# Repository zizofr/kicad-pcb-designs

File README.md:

# KiCad PCB Designs

Two PCB projects designed in KiCad: a digital voltmeter and a 220 V AC LED lamp. Each folder contains the KiCad project, the schematic, the PCB layout and a 3D render.

> **Design process:** both boards are my own designs, created in KiCad with AI-assisted guidance. I use AI as a tutor to learn circuit design, and I work through each block of the circuit to understand it.

## 1. Digital voltmeter (`voltmeter/`)

A voltmeter board built around an **ATmega328P** with a 16 MHz crystal and a 16x2 LCD.

- **Power:** 7805 regulator with reverse-polarity protection
- **Input stage:** resistor divider with a fuse, clamping diodes and a 5.1 V zener to protect the ADC
- **Programming:** ICSP header
- **Layout:** double-sided PCB with routed traces and a ground pour

**Status:** designed in KiCad. [Add whether you assembled and tested it, and the measurement range]

## 2. LED lamp (`led-lamp/`)

A compact LED lamp powered from the 220 V AC mains.

- **Rectification:** MB6S bridge rectifier
- **Lighting:** series string of SMD LEDs
- **Passive parts:** current-limiting and bleeder resistors, smoothing capacitors

**Status:** designed in KiCad. [Add whether you built or tested it]

> ⚠️ **Safety warning:** this circuit connects directly to 220 V mains and has no galvanic isolation. Every part of the circuit can be at mains potential. Do not build or touch it unless you know how to work safely with mains voltage. It is shared for educational purposes only.

## Tools

KiCad (schematic capture, PCB layout, 3D viewer)

## Author

Mohamed Aziz Farhani, IoT Engineering Student at ISITCom Hammam Sousse
[LinkedIn](https://www.linkedin.com/in/mohamed-aziz-farhani-18540a33a)

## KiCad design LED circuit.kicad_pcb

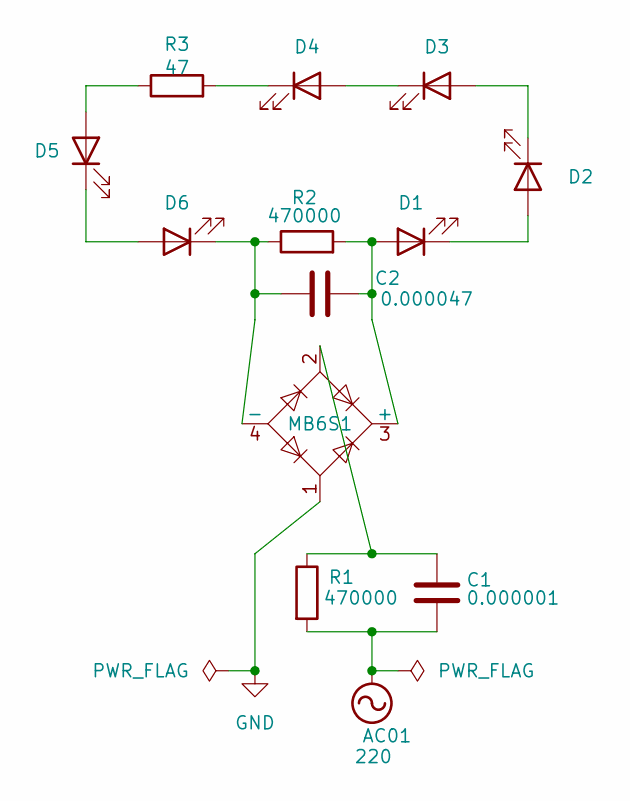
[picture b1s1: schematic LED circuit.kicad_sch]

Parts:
AC01: 220
C1: 0.000001; C_Rect_L18.0mm_W6.0mm_P15.00mm_FKS3_FKP3
C2: 0.000047; C_Radial_D6.3mm_H11.0mm_P2.50mm
D1, D2, D3, D4, D5, D6: LED; LED_PLCC_2835_Handsoldering
MB6S1: TO-269AA
R1, R2: 470000; R_0805_2012Metric_Pad1.20x1.40mm_HandSolder
R3: 47; R_1210_3225Metric_Pad1.30x2.65mm_HandSolder

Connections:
220: AC01.1, C1.2, R1.2
GND: MB6S1.1
unnamed: C1.1, MB6S1.2, R1.1
unnamed: C2.2, D1.2 (A), MB6S1.3 (+), R2.2
unnamed: D1.1 (K), D2.2 (A)
unnamed: D2.1 (K), D3.2 (A)
unnamed: D3.1 (K), D4.2 (A)
unnamed: D4.1 (K), R3.2
unnamed: D5.2 (A), R3.1
unnamed: D5.1 (K), D6.2 (A)
unnamed: C2.1, D6.1 (K), MB6S1.4 (-), R2.1

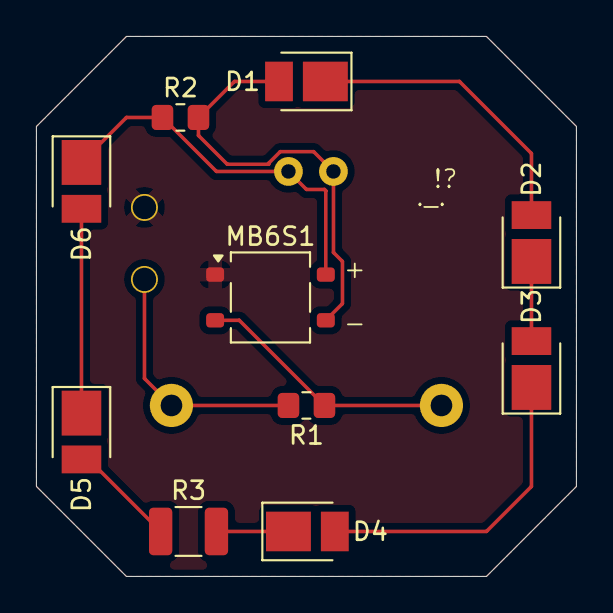
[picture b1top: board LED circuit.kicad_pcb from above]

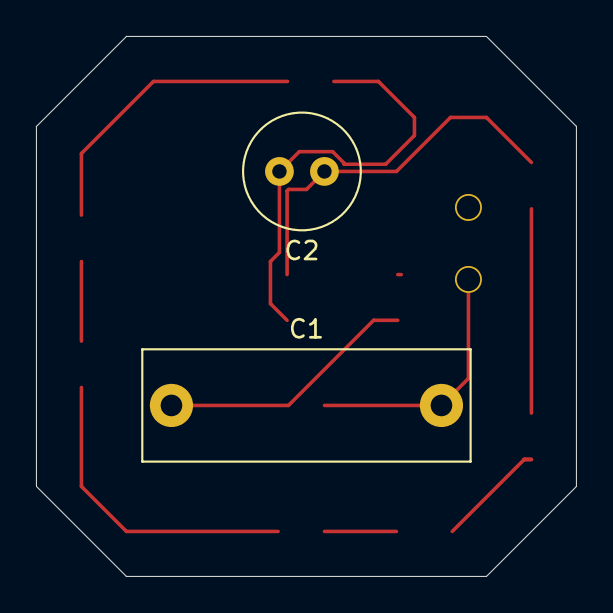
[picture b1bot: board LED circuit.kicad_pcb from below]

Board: 2 copper layers, 30.0 x 30.0 mm, 12 parts (2 on the bottom side), 10 nets.
